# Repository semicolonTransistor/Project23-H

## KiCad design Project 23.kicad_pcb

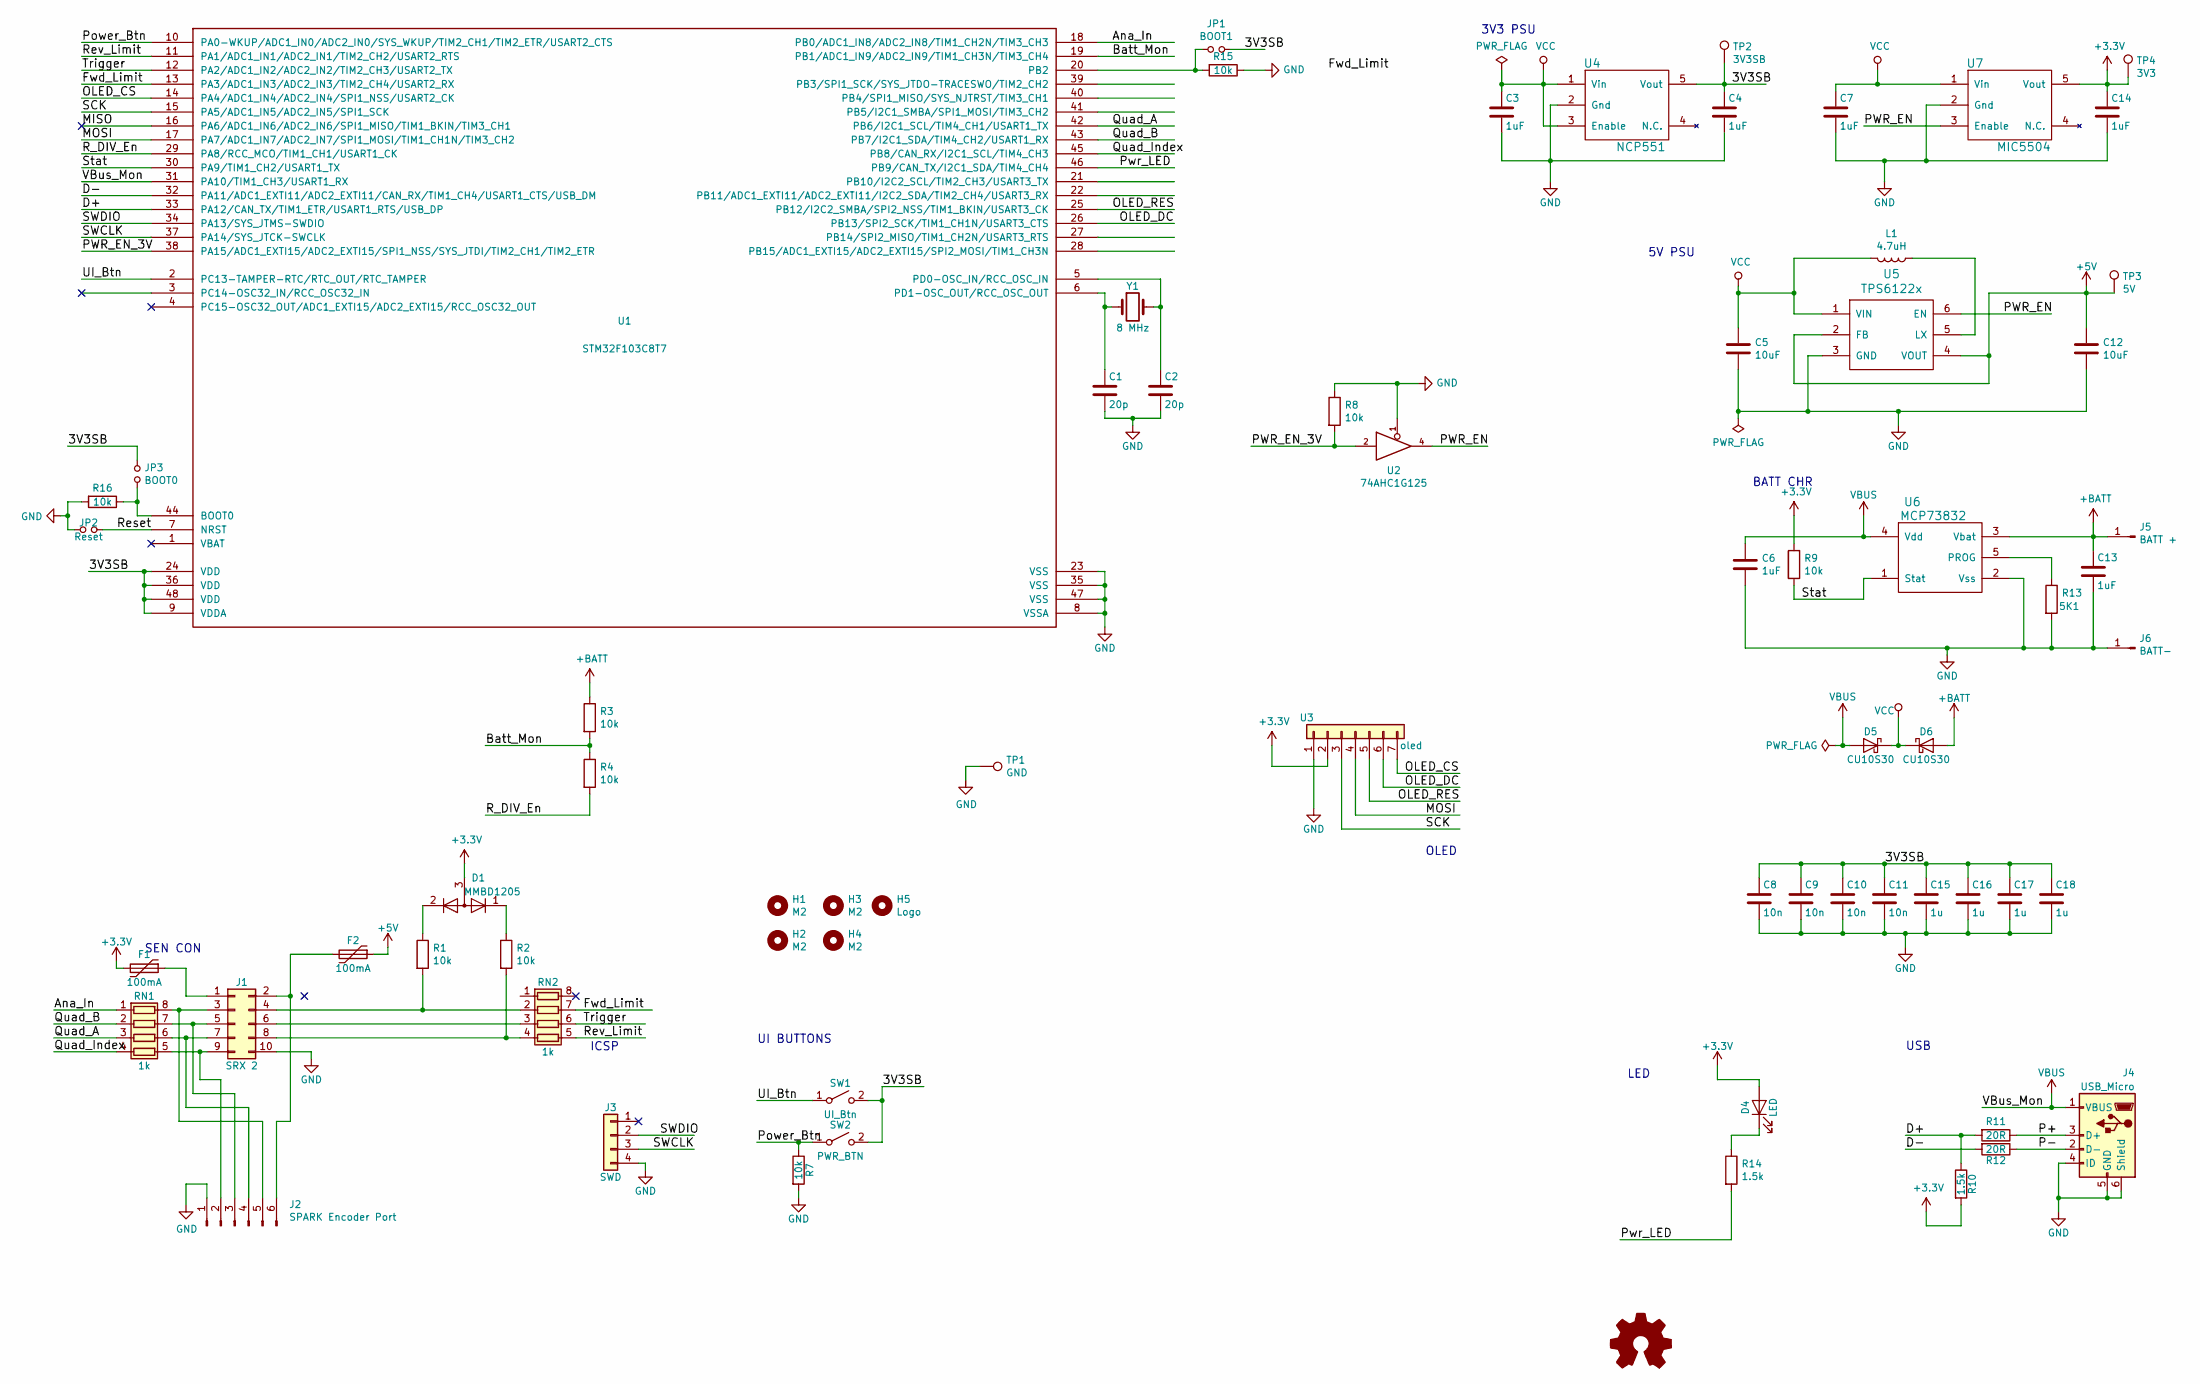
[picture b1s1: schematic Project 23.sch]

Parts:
C1, C2: 20p; C_0805_2012Metric_Pad1.15x1.40mm_HandSolder
C3, C4, C6, C7, C13, C14: 1uF; C_0805_2012Metric_Pad1.15x1.40mm_HandSolder
C5, C12: 10uF; C_0805_2012Metric_Pad1.15x1.40mm_HandSolder
C8, C9, C10, C11: 10n; C_0805_2012Metric_Pad1.15x1.40mm_HandSolder
C15, C16, C17, C18: 1u; C_0805_2012Metric_Pad1.15x1.40mm_HandSolder
D1: MMBD1205; SOT-23
D4: LED; LED_0805_2012Metric_Pad1.15x1.40mm_HandSolder
D5, D6: CU10S30; D_SOD-323_HandSoldering
F1, F2: 100mA; Fuse_1206_3216Metric_Pad1.42x1.75mm_HandSolder
H1, H2, H3, H4: M2; MountingHole_2.2mm_M2
H5: Logo; goldfish
J1: SRX 2; PinHeader_2x05_P1.27mm_Horizontal
J2: SPARK Encoder Port; JST_PH_S6B-PH-K_1x06_P2.00mm_Horizontal
J3: SWD; PinHeader_1x04_P2.54mm_Horizontal
J4: USB_Micro; microUsbSunken
J5: BATT +; PinHeader_1x01_P2.54mm_Vertical
J6: BATT-; PinHeader_1x01_P2.54mm_Vertical
JP1: BOOT1; SolderJumper-2_P1.3mm_Open_Pad1.0x1.5mm
JP2: Reset; SolderJumper-2_P1.3mm_Open_Pad1.0x1.5mm
JP3: BOOT0; SolderJumper-2_P1.3mm_Open_Pad1.0x1.5mm
L1: 4.7uH; L_1206_3216Metric_Pad1.42x1.75mm_HandSolder
R1, R2, R3, R4, R7, R8, R9, R15, R16: 10k; R_0805_2012Metric_Pad1.15x1.40mm_HandSolder
R10, R14: 1.5k; R_0805_2012Metric_Pad1.15x1.40mm_HandSolder
R11, R12: 20R; R_0805_2012Metric_Pad1.15x1.40mm_HandSolder
R13: 5K1; R_0805_2012Metric_Pad1.15x1.40mm_HandSolder
RN1, RN2: 1k; R_Array_Convex_4x0603
SW1: UI_Btn; SW_PUSH_6mm_H5mm
SW2: PWR_BTN; SW_PUSH_6mm_H5mm
TP1: GND; TestPoint_Pad_D2.0mm
TP2: 3V3SB; TestPoint_Pad_D2.0mm
TP3: 5V; TestPoint_Pad_D2.0mm
TP4: 3V3; TestPoint_Pad_D2.0mm
U1: STM32F103C8T7; LQFP-48_7x7mm_P0.5mm
U2: 74AHC1G125; SOT-23-5_HandSoldering
U3: oled; PinHeader_1x07_P2.54mm_Vertical
U4: NCP551; SOT-23-5_HandSoldering
U5: TPS6122x; SOT-363_SC-70-6_Handsoldering
U6: MCP73832; SOT-23-5_HandSoldering
U7: MIC5504; SOT-23-5_HandSoldering
Y1: 8 MHz; Crystal_SMD_Abracon_ABM3-2Pin_5.0x3.2mm_HandSoldering

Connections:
+3V3: C14.1, D1.3 (A), D4.2 (A), F1.2, R9.1, R10.2, TP4.1, U3.2, U7.5 (Vout)
+5V: C12.1, F2.1, TP3.1, U5.2 (FB), U5.4 (VOUT)
+BATT: C13.1, D6.2 (A), J5.1, R3.1, U6.3 (Vbat)
/3V3SB: C4.1, C8.1, C9.1, C10.1, C11.1, C15.1, C16.1, C17.1, C18.1, JP1.2, JP3.1, SW1.2 (B), SW2.2 (B), TP2.1, U1.9 (VDDA), U1.24 (VDD), U1.36 (VDD), U1.48 (VDD), U4.5 (Vout)
/Ana_In: RN1.1 (R1.1), U1.18 (PB0/ADC1_IN8/ADC2_IN8/TIM1_CH2N/TIM3_CH3)
/Batt_Mon: R3.2, R4.1, U1.19 (PB1/ADC1_IN9/ADC2_IN9/TIM1_CH3N/TIM3_CH4)
/D+: R10.1, R11.2, U1.33 (PA12/CAN_TX/TIM1_ETR/USART1_RTS/USB_DP)
/D-: R12.2, U1.32 (PA11/ADC1_EXTI11/ADC2_EXTI11/CAN_RX/TIM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)
/Fwd_Limit: RN2.7 (R2.2), U1.13 (PA3/ADC1_IN3/ADC2_IN3/TIM2_CH4/USART2_RX)
/MOSI: U1.17 (PA7/ADC1_IN7/ADC2_IN7/SPI1_MOSI/TIM1_CH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), U3.4
/OLED_CS: U1.14 (PA4/ADC1_IN4/ADC2_IN4/SPI1_NSS/USART2_CK), U3.7
/OLED_DC: U1.26 (PB13/SPI2_SCK/TIM1_CH1N/USART3_CTS), U3.6
/OLED_RES: U1.25 (PB12/I2C2_SMBA/SPI2_NSS/TIM1_BKIN/USART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), U3.5
/P+: J4.3 (D+), R11.1
/P-: J4.2 (D-), R12.1
/PWR_EN: U2.4, U5.6 (EN), U7.3 (Enable)
/PWR_EN_3V: R8.2, U1.38 (PA15/ADC1_EXTI15/ADC2_EXTI15/SPI1_NSS/S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), U2.2
/Power_Btn: R7.1, SW2.1 (A), U1.10 (PA0-WKUP/ADC1_IN0/ADC2_IN0/SYS_WKUP/TIM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)
/Pwr_LED: R14.2, U1.46 (PB9/CAN_TX/I2C1_SDA/TIM4_CH4)
/Quad_A: RN1.3 (R3.1), U1.42 (PB6/I2C1_SCL/TIM4_CH1/USART1_TX)
/Quad_B: RN1.2 (R2.1), U1.43 (PB7/I2C1_SDA/TIM4_CH2/USART1_RX)
/Quad_Index: RN1.4 (R4.1), U1.45 (PB8/CAN_RX/I2C1_SCL/TIM4_CH3)
/R_DIV_En: R4.2, U1.29 (PA8/RCC_MCO/TIM1_CH1/USART1_CK)
/Reset: JP2.2, U1.7 (NRST)
/Rev_Limit: RN2.5 (R4.2), U1.11 (PA1/ADC1_IN1/ADC2_IN1/TIM2_CH2/USART2_R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)
/SCK: U1.15 (PA5/ADC1_IN5/ADC2_IN5/SPI1_SCK), U3.3
/SWCLK: J3.3, U1.37 (PA14/SYS_JTCK-SWCLK)
/SWDIO: J3.2, U1.34 (PA13/SYS_JTMS-SWDIO)
/Stat: R9.2, U1.30 (PA9/TIM1_CH2/USART1_TX), U6.1 (Stat)
/Trigger: RN2.6 (R3.2), U1.12 (PA2/ADC1_IN2/ADC2_IN2/TIM2_CH3/USART2_TX)
/UI_Btn: SW1.1 (A), U1.2 (PC13-TAMPER-RTC/RTC_OUT/RTC_TAMPER)
GND: C1.2, C2.2, C3.2, C4.2, C5.2, C6.2, C7.2, C8.2, C9.2, C10.2, C11.2, C12.2, C13.2, C14.2, C15.2, C16.2, C17.2, C18.2, J1.10, J2.1, J3.4, J4.4 (ID), J4.5 (GND), J4.6 (Shield), J6.1, JP2.1, R7.2, R8.1, R13.2, R15.1, R16.2, TP1.1, U1.8 (VSSA), U1.23 (VSS), U1.35 (VSS), U1.47 (VSS), U2.1, U2.3 (GND), U3.1, U4.2 (Gnd), U5.3 (GND), U6.2 (Vss), U7.2 (Gnd)
unnamed: C1.1, U1.6 (PD1-OSC_OUT/RCC_OSC_OUT), Y1.1
unnamed: C2.1, U1.5 (PD0-OSC_IN/RCC_OSC_IN), Y1.2
unnamed: D1.1 (K), R2.1
unnamed: D1.2 (K), R1.1
unnamed: D4.1 (K), R14.1
unnamed: F1.1, J1.1
unnamed: F2.2, J1.2, J2.6
unnamed: J1.3, J2.5, RN1.8 (R1.2)
unnamed: J1.4, R1.2, RN2.2 (R2.1)
unnamed: J1.5, J2.3, RN1.7 (R2.2)
unnamed: J1.6, RN2.3 (R3.1)
unnamed: J1.7, J2.4, RN1.6 (R3.2)
unnamed: J1.8, R2.2, RN2.4 (R4.1)
unnamed: J1.9, J2.2, RN1.5 (R4.2)
unnamed: JP1.1, R15.2, U1.20 (PB2)
unnamed: JP3.2, R16.1, U1.44 (BOOT0)
unnamed: L1.1, U5.5 (LX)
unnamed: R13.1, U6.5 (PROG)
VBUS: C6.1, D5.2 (A), J4.1 (VBUS), U1.31 (PA10/TIM1_CH3/USART1_RX), U6.4 (Vdd)
VCC: C3.1, C5.1, C7.1, D5.1 (K), D6.1 (K), L1.2, U2.5 (VCC), U4.1 (Vin), U4.3 (Enable), U5.1 (VIN), U7.1 (Vin)

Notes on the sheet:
LED
USB
5V PSU
BATT CHR
OLED
UI BUTTONS
SEN CON
ICSP
3V3 PSU

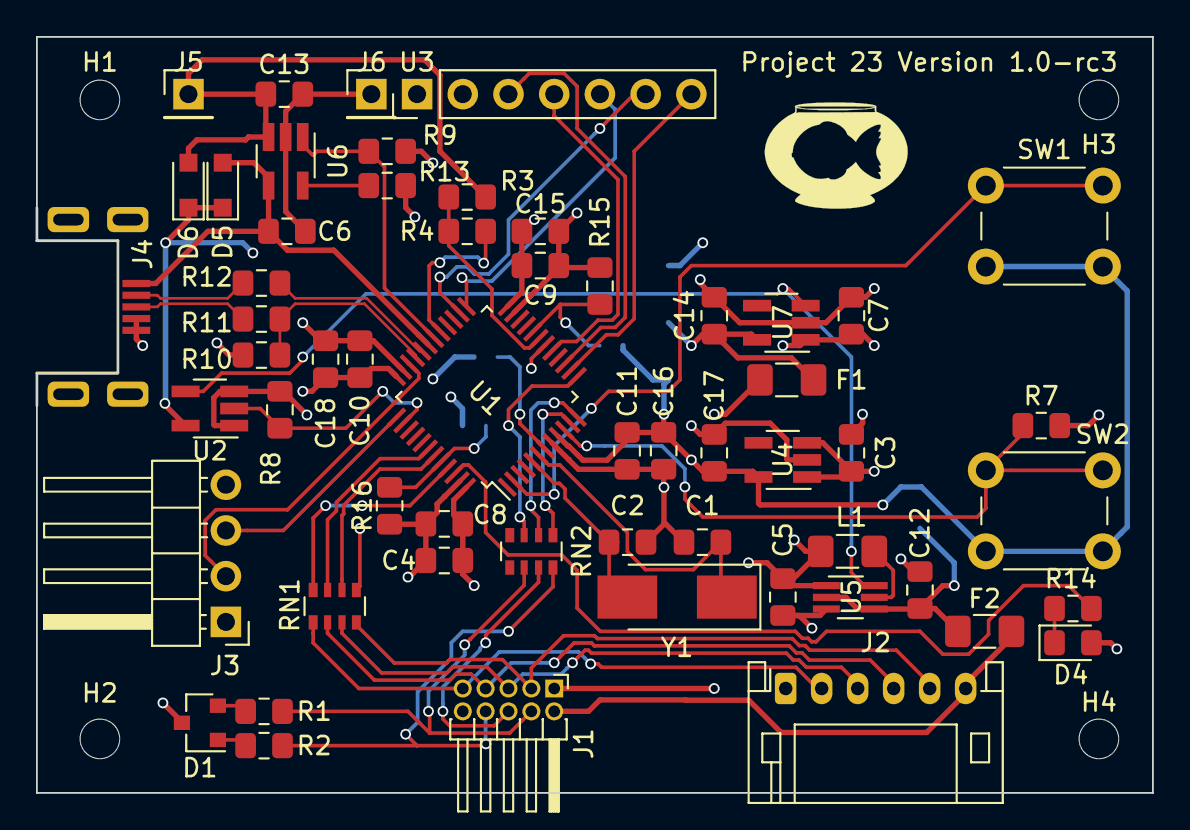
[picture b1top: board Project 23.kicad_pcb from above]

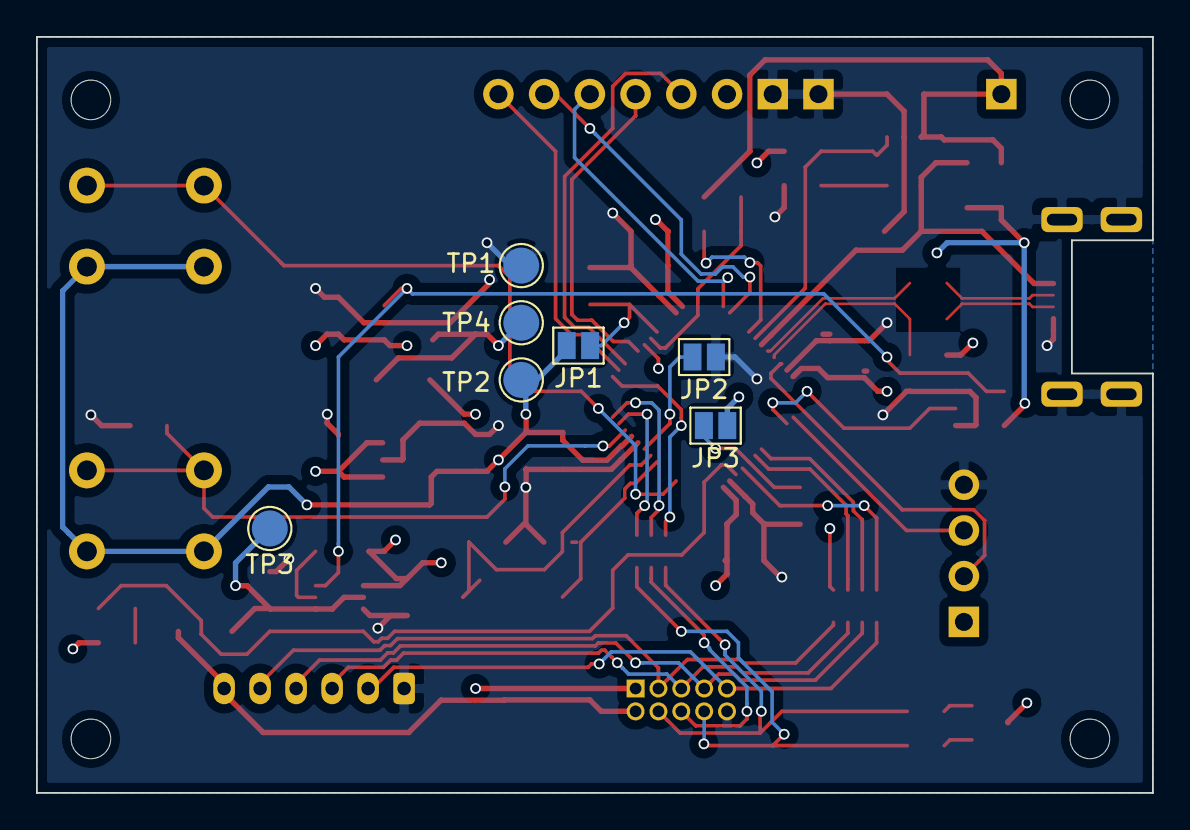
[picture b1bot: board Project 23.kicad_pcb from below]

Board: 4 copper layers, 62.0 x 42.0 mm, 69 parts (7 on the bottom side), 52 nets.

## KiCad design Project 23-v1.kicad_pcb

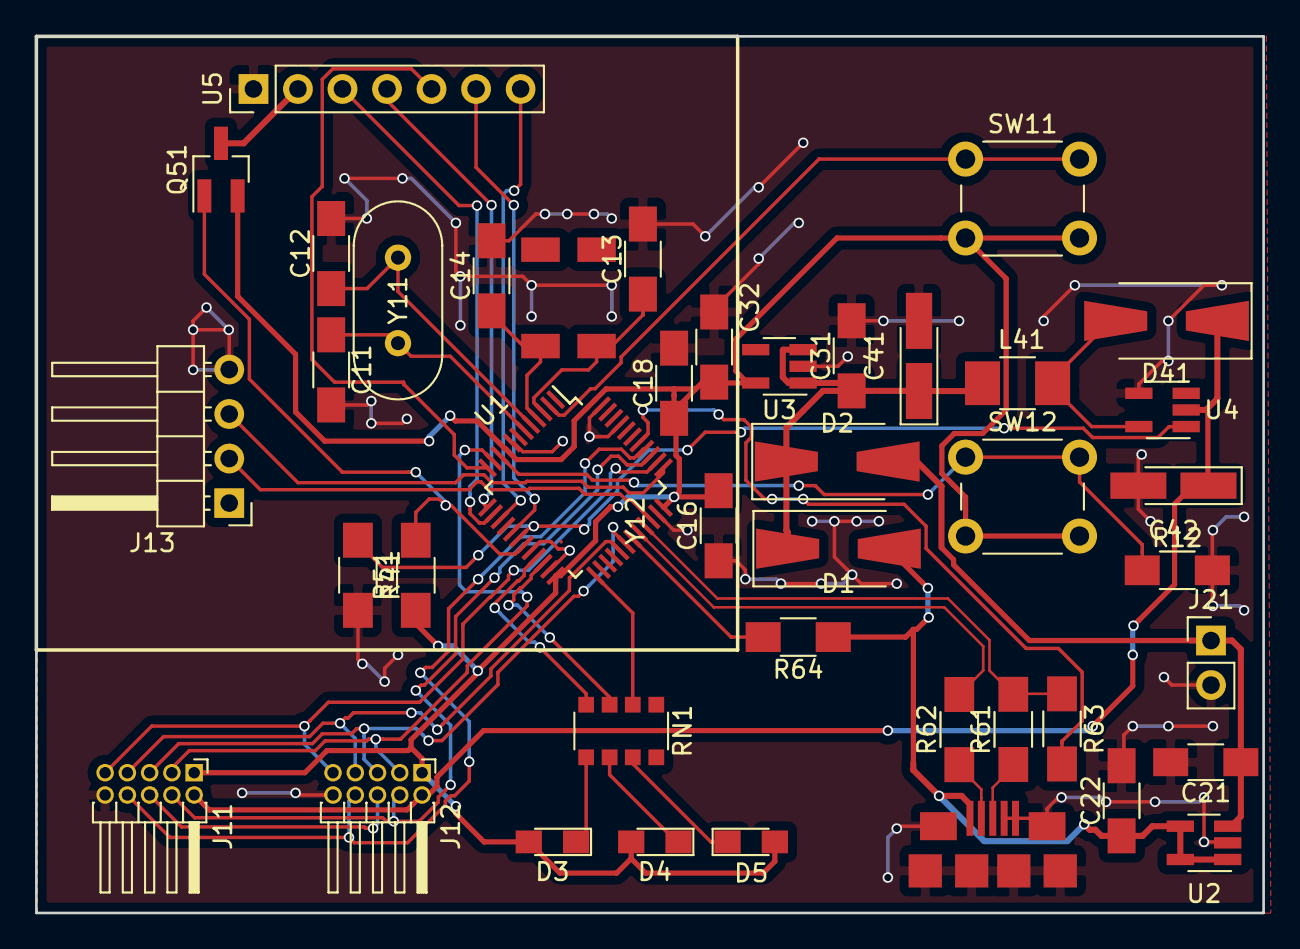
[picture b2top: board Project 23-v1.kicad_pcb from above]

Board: 2 copper layers, 70.0 x 50.0 mm, 42 parts (0 on the bottom side), 42 nets.

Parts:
C11, C12, C13, C14: 20p; C_1206_HandSoldering
C16, C18: 0.1uF; C_1206_HandSoldering
C21, C22, C31, C32: 1uF; C_1206_HandSoldering
C41: 10uF,Tan; CP_Tantalum_Case-A_EIA-3216-18_Hand
C42: 47uF,Tan; CP_Tantalum_Case-A_EIA-3216-18_Hand
D1, D2, D41: MBRS140; D_SMA-SMB_Universal_Handsoldering
D3, D4, D5: LED; LED_0805_HandSoldering
J11: SRX 1; Pin_Header_Angled_2x05_Pitch1.27mm
J12: SRX 2; Pin_Header_Angled_2x05_Pitch1.27mm
J13: SWD; Pin_Header_Angled_1x04_Pitch2.54mm
J21: Batt; Pin_Header_Straight_1x02_Pitch2.54mm
J61: USB_Micro; usbMicro
L41: 47uH; R_1210_HandSoldering
Q51: Si2315; SOT-23_Handsoldering
R12, R41, R51, R64: 10k; R_1206_HandSoldering
R61, R62: 20R; R_1206_HandSoldering
R63: 1.5k; R_1206_HandSoldering
RN1: 1k; R_Array_Convex_4x1206
SW11: UI_Btn; SW_PUSH_6mm
SW12: SW_SPST; SW_PUSH_6mm
U1: STM32F103C(8-B)Tx; LQFP-48_7x7mm_Pitch0.5mm
U2: MCP73811; SOT-23-5_HandSoldering
U3: NCP551; SOT-23-5_HandSoldering
U4: NCP1402; SOT-23-5_HandSoldering
U5: oled; Pin_Header_Straight_1x07_Pitch2.54mm
Y11: 8 MHz; Crystal_HC49-U_Vertical
Y12: 32khz; ABS25

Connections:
+3V3: C16.1, C18.1, C32.1, D3.2, D4.2, D5.2, J11.1, J12.1, Q51.2, R51.1, SW11.2, SW12.2, U1.9, U1.24, U1.36, U1.48, U3.5
+5V: C42.1, D41.1, J11.2, J12.2, U4.2
+BATT: C21.1, D2.2, J21.1, U2.3
/Ana_In: J11.3, J12.3, U1.11
/Boost_En: R41.1, U1.18, U4.1
/D+: R61.2, R63.1, U1.33
/D-: R62.2, U1.32
/Fwd_LED: RN1.4, U1.21
/Fwd_Limit: J11.4, J12.4, U1.39
/MOSI: U1.17, U5.6
/OLED_CS: U1.14, U5.3
/OLED_DC: U1.13, U5.4
/OLED_En: Q51.1, R51.2, U1.19
/OLED_RES: U1.12, U5.5
/P+: J61.3, R61.1
/P-: J61.2, R62.1
/Power_Btn: R12.1, SW12.1, U1.10
/Pwr_LED: RN1.2, U1.25
/Quad_A: J11.7, J12.7, U1.29
/Quad_B: J11.5, J12.5, U1.30
/Quad_Index: J11.9, J12.9, U1.38
/Rev_LED: RN1.3, U1.22
/Rev_Limit: J11.8, J12.8, U1.40
/SCK: U1.15, U5.7
/SWCLK: J13.3, U1.37
/SWDIO: J13.2, U1.34
/UI_Btn: SW11.1, U1.2
/USB_PU: R63.2, U1.41
/VBus_Sense: R64.2, U1.31
GND: C11.2, C12.2, C13.2, C14.2, C16.2, C18.2, C21.2, C22.2, C31.2, C32.2, C41.2, C42.2, J11.10, J12.10, J13.4, J21.2, J61.4, J61.5, J61.6, R12.2, R41.2, U1.8, U1.20, U1.23, U1.35, U1.44, U1.47, U2.2, U3.2, U4.4, U5.1
unnamed: C11.1, U1.6, Y11.1
unnamed: C12.1, U1.5, Y11.2
unnamed: C13.1, U1.3, Y12.1
unnamed: C14.1, U1.4, Y12.2
unnamed: D3.1, RN1.5
unnamed: D4.1, RN1.6
unnamed: D5.1, RN1.7
unnamed: D41.2, L41.1, U4.5
unnamed: J11.6, J12.6
unnamed: Q51.3, U5.2
VBUS: C22.1, D1.2, J61.1, R64.1, U2.1, U2.4, U2.5
VDD: C31.1, C41.1, D1.1, D2.1, L41.2, U3.1, U3.3

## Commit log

2018-06-24 Inital Commit, Version 0.2
2018-07-10 Fixed solder mask expansion ensured solder mask bridges between all pads of 0.5mm pitch LQFP-48 footprint. bumped revision to 0.4.
    更正了阻焊开窗大小。 现在在0.5mm间距的LQFP-48封装的每个焊盘间都有阻焊桥。将版本提升至0.4。
2018-10-03 Removed old files.
2018-10-03 Oled Connector fixed
    Update to Version 0.4
    Fixed oled connector
2018-10-05 Version 0.5
    Removed 32k osc and added monting holes.
2018-10-07 Reorganized sch
    Move Sch over to a larger page, added physical drawing of borad.
2018-10-08 Updated footprints to Kicad 5.0.0 librarys
    Updated footprints to Kicad 5.0.0 Libraries. Switched C41 and C42 to EIA 3528-21 and EIA 6032-28 respectively.
2018-10-09 Generated up to date gerber
2018-12-02 0.7 Schmatic Design
    Added SD card for logging, Updated 3.3V power supplies to accont for addational power required by the sd card. Added battery voltage messurment. Replaced battery charge IC with one that has a charge 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
2018-12-02 Delete Project 23.bak
    Remove temp file from repo
2018-12-02 Delete Project 23-rescue.lib
    Remove temp file from repo.
2018-12-02 Delete Project 23.kicad_pcb-bak
    Remove temp file from repo.
2018-12-02 Delete Project23-extras.bak
    Remove temp file from repo.
2018-12-02 Delete Project23-extras.bck
    Remove temp file from repo.
2018-12-02 Added Serial connector
    added serial connector
2018-12-02 Delete Project 23.net
    Remove generated net file
2018-12-02 Delete Project 23.xml
    Remove generated bom file.
2018-12-02 Finished sunken micro-usb socket
2018-12-06 Finished footprint for micro SD holder
2018-12-06 Completed V0.7 PCB Design
2018-12-15 Final prototype v0.7
    Added logo, replaced NCP1402 as it is EOL.
2019-01-11 Power Routed
2019-01-11 Power lines routed
2019-01-12 Minor routing changes
2019-01-21 Reworked USB Socket
2019-01-21 Added USB traces
2019-01-23 Updated SRX connectors
2019-01-23 Update Project 23.kicad_pcb
    Locked components
2019-01-24 Created bom and regenerated gerber files
2019-02-19 Inital steps
2019-04-22 4 Layer with reworked layout
2019-04-23 Added logo and rearraged silkscreen
